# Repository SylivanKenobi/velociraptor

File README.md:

# Vleociraptor

A 5x12 Ortholinear low-profile qmk compatible Keyboard. The Keyboard only uses through hole components.

BOM:
* [Controller](https://splitkb.com/products/pro-micro-atmega32u4-5v-16mhz)
* [Diodes](https://splitkb.com/products/tht-diodes)

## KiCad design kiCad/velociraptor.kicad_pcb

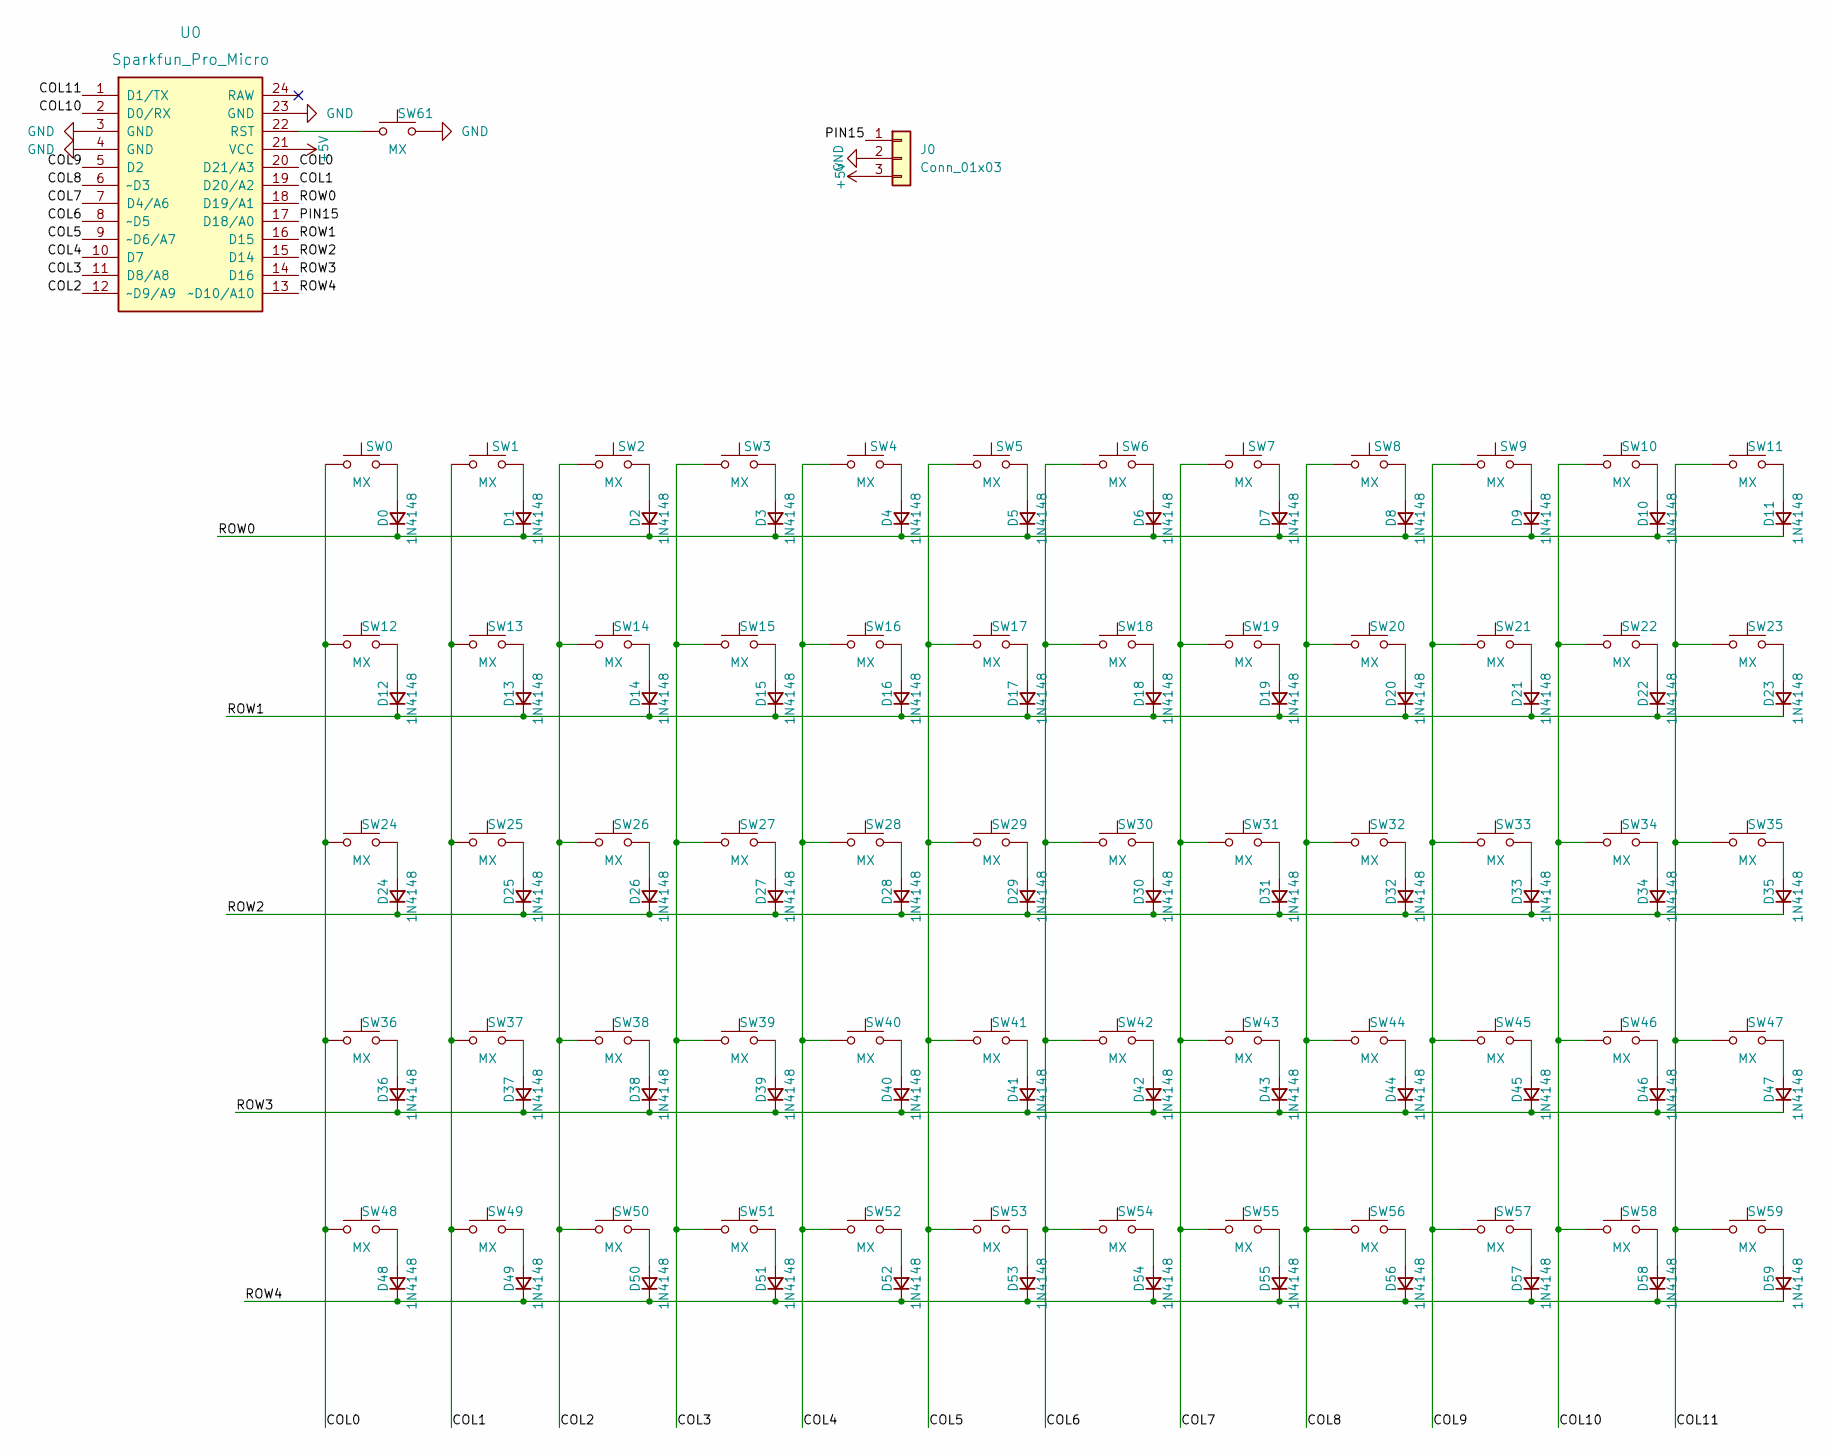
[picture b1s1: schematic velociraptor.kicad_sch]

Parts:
D0, D1, D2, D3, D4, D5, D6, D7, D8, D9, D10, D11, D12, D13, D14, D15, D16, D17, D18, D19, D20, D21, D22, D23, D24, D25, D26, D27, D28, D29, D30, D31, D32, D33, D34, D35, D36, D37, D38, D39, D40, D41, D42, D43, D44, D45, D46, D47, D48, D49, D50, D51, D52, D53, D54, D55, D56, D57, D58, D59: 1N4148; D_DO-35_SOD27_P7.62mm_Horizontal
J0: Conn_01x03; PinHeader_1x03_P2.54mm_Vertical
SW0, SW1, SW2, SW3, SW4, SW5, SW6, SW7, SW8, SW9, SW10, SW11, SW12, SW13, SW14, SW15, SW16, SW17, SW18, SW19, SW20, SW21, SW22, SW23, SW24, SW25, SW26, SW27, SW28, SW29, SW30, SW31, SW32, SW33, SW34, SW35, SW36, SW37, SW38, SW39, SW40, SW41, SW42, SW43, SW44, SW45, SW46, SW47, SW48, SW49, SW50, SW51, SW52, SW53, SW54, SW55, SW56, SW57, SW58, SW59: MX; Kailh-PG1350-1u-NoLED
SW61: MX; PushButton_6x6mm_TH_Pretty
U0: Sparkfun_Pro_Micro; ArduinoProMicro

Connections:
+5V: J0.3, U0.21 (VCC)
/COL0: SW0.1, SW12.1, SW24.1, SW36.1, SW48.1, U0.20 (D21/A3)
/COL1: SW1.1, SW13.1, SW25.1, SW37.1, SW49.1, U0.19 (D20/A2)
/COL2: SW2.1, SW14.1, SW26.1, SW38.1, SW50.1, U0.12 (~D9/A9)
/COL3: SW3.1, SW15.1, SW27.1, SW39.1, SW51.1, U0.11 (D8/A8)
/COL4: SW4.1, SW16.1, SW28.1, SW40.1, SW52.1, U0.10 (D7)
/COL5: SW5.1, SW17.1, SW29.1, SW41.1, SW53.1, U0.9 (~D6/A7)
/COL6: SW6.1, SW18.1, SW30.1, SW42.1, SW54.1, U0.8 (~D5)
/COL7: SW7.1, SW19.1, SW31.1, SW43.1, SW55.1, U0.7 (D4/A6)
/COL8: SW8.1, SW20.1, SW32.1, SW44.1, SW56.1, U0.6 (~D3)
/COL9: SW9.1, SW21.1, SW33.1, SW45.1, SW57.1, U0.5 (D2)
/COL10: SW10.1, SW22.1, SW34.1, SW46.1, SW58.1, U0.2 (D0/RX)
/COL11: SW11.1, SW23.1, SW35.1, SW47.1, SW59.1, U0.1 (D1/TX)
/PIN15: J0.1, U0.17 (D18/A0)
/ROW0: D0.1 (K), D1.1 (K), D2.1 (K), D3.1 (K), D4.1 (K), D5.1 (K), D6.1 (K), D7.1 (K), D8.1 (K), D9.1 (K), D10.1 (K), D11.1 (K), U0.18 (D19/A1)
/ROW1: D12.1 (K), D13.1 (K), D14.1 (K), D15.1 (K), D16.1 (K), D17.1 (K), D18.1 (K), D19.1 (K), D20.1 (K), D21.1 (K), D22.1 (K), D23.1 (K), U0.16 (D15)
/ROW2: D24.1 (K), D25.1 (K), D26.1 (K), D27.1 (K), D28.1 (K), D29.1 (K), D30.1 (K), D31.1 (K), D32.1 (K), D33.1 (K), D34.1 (K), D35.1 (K), U0.15 (D14)
/ROW3: D36.1 (K), D37.1 (K), D38.1 (K), D39.1 (K), D40.1 (K), D41.1 (K), D42.1 (K), D43.1 (K), D44.1 (K), D45.1 (K), D46.1 (K), D47.1 (K), U0.14 (D16)
/ROW4: D48.1 (K), D49.1 (K), D50.1 (K), D51.1 (K), D52.1 (K), D53.1 (K), D54.1 (K), D55.1 (K), D56.1 (K), D57.1 (K), D58.1 (K), D59.1 (K), U0.13 (~D10/A10)
GND: J0.2, SW61.2, U0.3 (GND), U0.4 (GND), U0.23 (GND)
unnamed: D0.2 (A), SW0.2
unnamed: D1.2 (A), SW1.2
unnamed: D2.2 (A), SW2.2
unnamed: D3.2 (A), SW3.2
unnamed: D4.2 (A), SW4.2
unnamed: D5.2 (A), SW5.2
unnamed: D6.2 (A), SW6.2
unnamed: D7.2 (A), SW7.2
unnamed: D8.2 (A), SW8.2
unnamed: D9.2 (A), SW9.2
unnamed: D10.2 (A), SW10.2
unnamed: D11.2 (A), SW11.2
unnamed: D12.2 (A), SW12.2
unnamed: D13.2 (A), SW13.2
unnamed: D14.2 (A), SW14.2
unnamed: D15.2 (A), SW15.2
unnamed: D16.2 (A), SW16.2
unnamed: D17.2 (A), SW17.2
unnamed: D18.2 (A), SW18.2
unnamed: D19.2 (A), SW19.2
unnamed: D20.2 (A), SW20.2
unnamed: D21.2 (A), SW21.2
unnamed: D22.2 (A), SW22.2
unnamed: D23.2 (A), SW23.2
unnamed: D24.2 (A), SW24.2
unnamed: D25.2 (A), SW25.2
unnamed: D26.2 (A), SW26.2
unnamed: D27.2 (A), SW27.2
unnamed: D28.2 (A), SW28.2
unnamed: D29.2 (A), SW29.2
unnamed: D30.2 (A), SW30.2
unnamed: D31.2 (A), SW31.2
unnamed: D32.2 (A), SW32.2
unnamed: D33.2 (A), SW33.2
unnamed: D34.2 (A), SW34.2
unnamed: D35.2 (A), SW35.2
unnamed: D36.2 (A), SW36.2
unnamed: D37.2 (A), SW37.2
unnamed: D38.2 (A), SW38.2
unnamed: D39.2 (A), SW39.2
unnamed: D40.2 (A), SW40.2
unnamed: D41.2 (A), SW41.2
unnamed: D42.2 (A), SW42.2
unnamed: D43.2 (A), SW43.2
unnamed: D44.2 (A), SW44.2
unnamed: D45.2 (A), SW45.2
unnamed: D46.2 (A), SW46.2
unnamed: D47.2 (A), SW47.2
unnamed: D48.2 (A), SW48.2
unnamed: D49.2 (A), SW49.2
unnamed: D50.2 (A), SW50.2
unnamed: D51.2 (A), SW51.2
unnamed: D52.2 (A), SW52.2
unnamed: D53.2 (A), SW53.2
unnamed: D54.2 (A), SW54.2
unnamed: D55.2 (A), SW55.2
unnamed: D56.2 (A), SW56.2
unnamed: D57.2 (A), SW57.2
unnamed: D58.2 (A), SW58.2
unnamed: D59.2 (A), SW59.2
unnamed: SW61.1, U0.22 (RST)

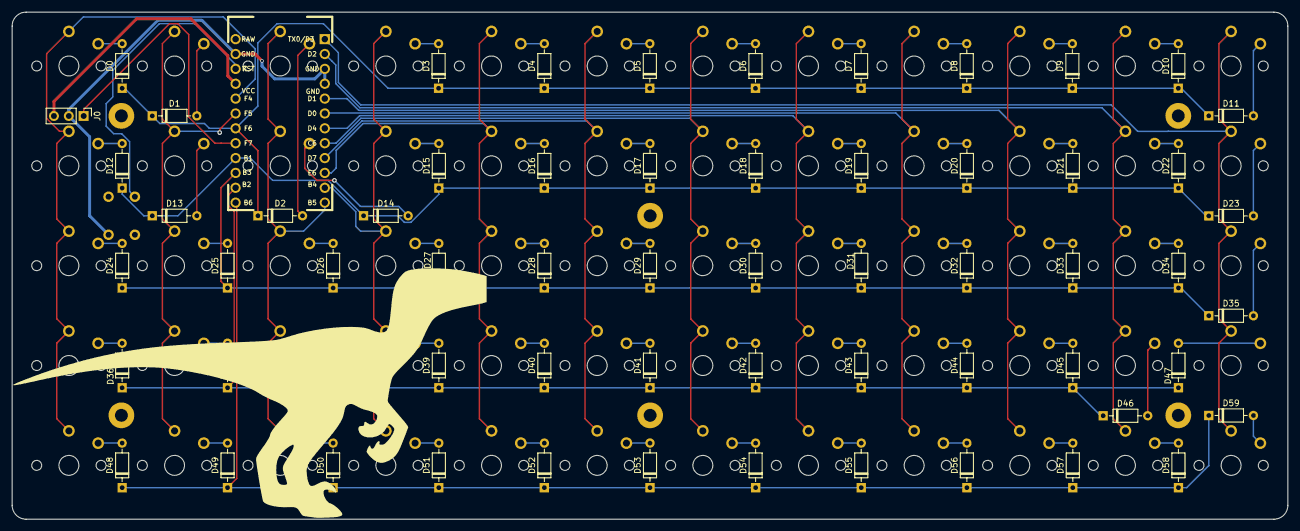
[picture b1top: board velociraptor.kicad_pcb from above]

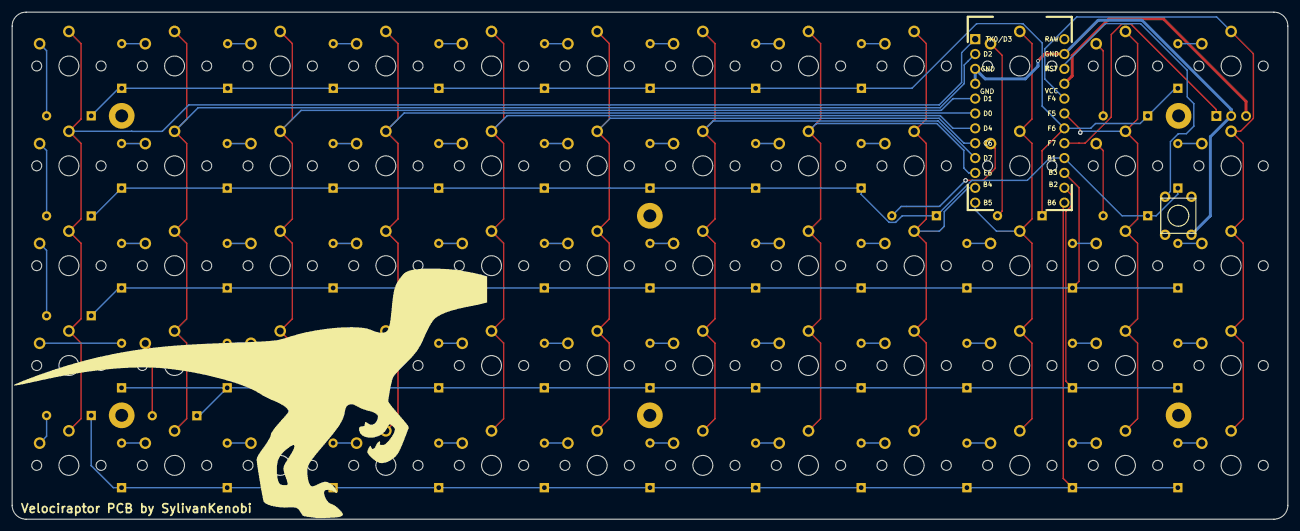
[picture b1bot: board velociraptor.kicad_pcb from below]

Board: 2 copper layers, 218.0 x 86.6 mm, 123 parts (2 on the bottom side), 81 nets.

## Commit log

2023-04-06 add kiCad files
2023-04-09 remove unused libraries, update to kicad 7, cleanup silkscreens
2023-04-09 cleanup repo
2023-04-09 add image, fix lib
2023-04-14 fix diode orientation
